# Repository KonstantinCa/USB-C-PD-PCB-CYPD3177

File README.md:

# USB-C Power Delivery PCB

**Note:** This project was developed as part of a university project. Technical references and documentation from the relevant companies/manufacturers, especially Infineon/Cypress documentation for the CYPD3177 USB-PD controller, were used as supporting sources for the design and analysis. The project is for educational and documentation purposes only.

This project focuses on the design and analysis of a USB-C Power Delivery sink system.  
The goal was to develop a custom PCB capable of requesting defined USB-PD voltage profiles from a USB-C Power Delivery charger.

The system is based on the Infineon/Cypress CYPD3177 USB-PD controller.  
An external microcontroller communicates with the controller via I2C in order to select different Power Delivery profiles and read status information such as the negotiated VBUS voltage.

## Project Overview

The project combines hardware design, embedded firmware and protocol analysis.  
The custom PCB was designed in KiCad and includes the required USB-C connector, USB-PD controller, power path circuitry, voltage regulation and communication interfaces.

## Features

- USB-C Power Delivery sink implementation
- CYPD3177 USB-PD controller integration
- Selection of different USB-PD voltage profiles
- I2C communication between microcontroller and USB-PD controller
- VBUS voltage measurement
- Interrupt-based response handling
- Finite State Machine firmware structure
- KiCad schematic and PCB layout
- Analysis of USB-PD, USB 2.0, I2C and UART communication

## Supported USB-PD Profiles

The firmware supports the following fixed supply PDO profiles:

| Profile | Voltage | Current |
|---|---:|---:|
| 1 | 5 V | 2 A |
| 2 | 9 V | 2 A |
| 3 | 12 V | 2.25 A |
| 4 | 15 V | 1.8 A |
| 5 | 20 V | 1.5 A |

## Firmware

The ESP32 firmware communicates with the CYPD3177 over I2C and allows the user to select a desired USB-PD profile via the serial monitor.

### Serial Commands

| Command | Function |
|---|---|
| `STATUS` | Reads the current status and response information |
| `5V2A` | Requests 5 V / 2 A |
| `9V2A` | Requests 9 V / 2 A |
| `12V2.25A` | Requests 12 V / 2.25 A |
| `15V1.8A` | Requests 15 V / 1.8 A |
| `20V1.5A` | Requests 20 V / 1.5 A |

### Firmware State Machine

The firmware is structured as a finite state machine:

```text
INIT -> IDLE -> SEND -> WAIT -> RECEIVE -> IDLE

The state machine waits for user input, checks whether a USB-PD contract is established, sends the selected PDO to the CYPD3177, waits for an interrupt, and then reads the response and VBUS voltage.

## Hardware Design

The PCB design contains the following main functional blocks:

- USB-C connector
- CYPD3177 USB Power Delivery controller
- Power path switching stage
- Buck converter for 3.3 V supply generation
- USB-to-UART interface for communication and debugging
- Microcontroller interface
- I2C communication lines
- UART communication lines
- Protection and configuration circuitry

The PCB was designed as a four-layer board with separate layers for signal routing, ground reference, and power distribution.

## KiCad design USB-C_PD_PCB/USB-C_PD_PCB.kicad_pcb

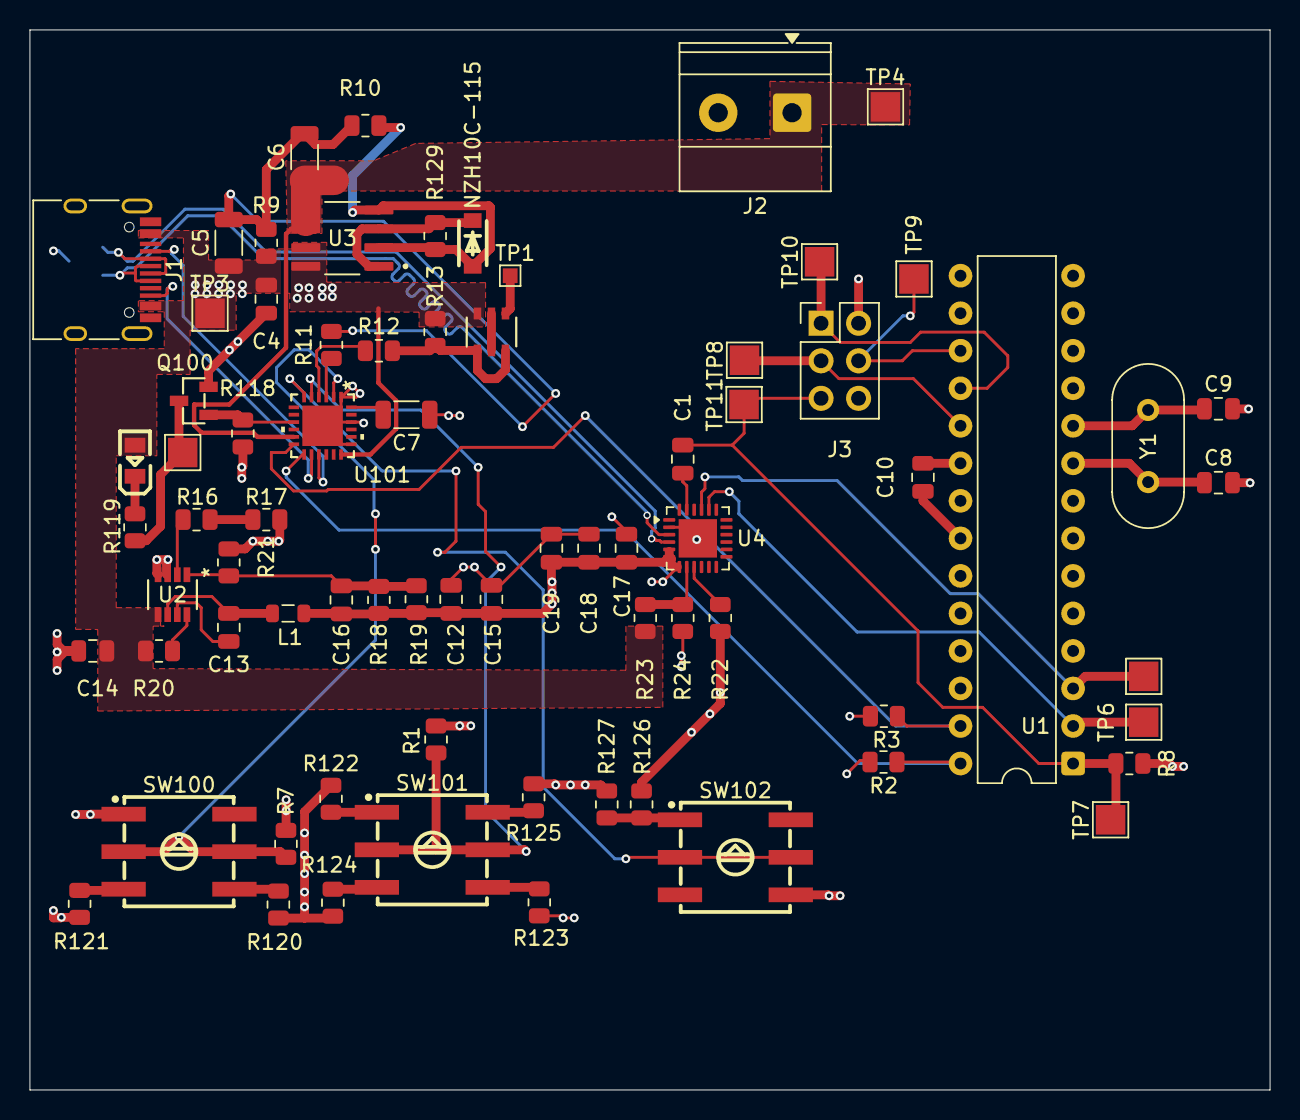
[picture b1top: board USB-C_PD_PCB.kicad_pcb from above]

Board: 4 copper layers, 83.9 x 71.8 mm, 75 parts (1 on the bottom side), 49 nets.

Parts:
BSL308PEH6327XTSA1: BSL308PEH6327XTSA1; PG-TSOP6-6-4_INF
C1: 4.7uF; C_0805_2012Metric
C4: 3.3uF; C_0805_2012Metric
C5, C6: 1uF; L_1206_3216Metric
C7: 100nF; L_1206_3216Metric
C8, C9: 22pF; C_0805_2012Metric
C10: ´10uF; C_0805_2012Metric
C12, C14, C15: 4u7; C_0805_2012Metric
C13: 100n; C_0805_2012Metric
C16: 10p; C_0805_2012Metric
C17, C18, C19: 100nF; C_0805_2012Metric
D1: ESDA5V3L; SOT-23-3
D101: LED PD; LED0805-R-RD
J1: USB4105-GF-A-060; USB_C_Receptacle_HRO_TYPE-C-31-M-12
J2: Screw_Terminal_01x02; TerminalBlock_Phoenix_MKDS-1,5-2_1x02_P5.00mm_Horizontal
J3: AVR-ISP-6; PinHeader_2x03_P2.54mm_Vertical
L1: 47u; L_0805_2012Metric
NZH10C-115: Zener Diode; SOD-123F_L2.8-W1.8-LS3.7-RD
Q100: NTR4503N; NTR4503NT1G-VB
R1, R7: 5k1; R_0805_2012Metric
R2, R3, R119: 1K; R_0805_2012Metric
R8, R11, R12, R22, R120: 1k; R_0805_2012Metric
R9: 10k; R_0805_2012Metric
R10: 0R; R_0805_2012Metric
R13: 49.9k; R_0805_2012Metric
R16, R17: 100k; R_0805_2012Metric
R18, R19: 2M; R_0805_2012Metric
R20: 20k; R_0805_2012Metric
R21: 222K; R_0805_2012Metric
R23: 180k; R_0805_2012Metric
R24: 33K; R_0805_2012Metric
R118: 100K 5%; R_0805_2012Metric
R121: 2.4k; R_0805_2012Metric
R122: 1 k; R_0805_2012Metric
R123, R127: 2.4 k; R_0805_2012Metric
R124, R126: 5.1 k; R_0805_2012Metric
R125: 10 k; R_0805_2012Metric
R129: 49.9K; R_0805_2012Metric
SW100: VBUS_Max; SW-SMD_MSSR-10S
SW101: Sink_Coarse; SW-SMD_MSSR-10S
SW102: Sink_fine; SW-SMD_MSSR-10S
TP1: TestPoint 5V; TestPoint_Pad_1.0x1.0mm
TP2, TP3, TP4, TP5, TP6, TP7, TP8, TP9, TP10, TP11: TestPoint; TestPoint_Pad_2.0x2.0mm
U1: ATmega328-P; DIP-28_W7.62mm
U2: SY8303AIC; TSOT_303AIC_SGY
U3: IRF9362TRPBF; SOIC127P600X175-8N
U4: CP2102N-Axx-xQFN24; QFN-24-1EP_4x4mm_P0.5mm_EP2.6x2.6mm
U101: CYPD3177-24LQXQT; QFN24_CYPD3177_INF
Y1: 8MHz; Crystal_HC49-U_Vertical

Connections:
+3.3V: C12.1, C15.1, C16.1, C17.1, C18.1, C19.1, J3.2 (VCC), L1.2, R1.1, R2.2, R3.2, R7.1, R8.2, R18.1, R19.1, R22.1, R126.1, U1.7 (VCC), U4.5 (VIO), U4.6 (VDD), U4.7 (VREGIN)
/GATE: NZH10C-115.2 (A), R10.1, R129.2, U3.2 (G1), U3.4 (G2)
/R_I_1A: R122.1, SW101.1
/R_I_2A: R123.1, SW101.2
/R_I_3A: R124.1, SW101.4
/R_I_4A: R125.1, SW101.8
/R_I_+500mA: R126.2, R127.1, SW102.1
/R_V_9V: R120.1, SW100.2
/R_V_12V: R121.1, SW100.4
/SOURCE: NZH10C-115.1 (K), R129.1, U3.1 (S1), U3.3 (S2)
CC1: J1.A5 (CC1), U101.15 (CC1)
CC2: J1.B5 (CC2), U101.14 (CC2)
D+: D1.2 (K), J1.A6 (DP1), J1.B6 (DP2), U4.3 (D+)
D-: D1.1 (K), J1.A7 (DN1), J1.B7 (DN2), U4.4 (D-)
GND: C4.1, C7.1, C8.2, C9.2, C10.2, C12.2, C14.2, C15.2, C17.2, C18.2, C19.2, D1.3 (A), J1.A1, J1.A12, J1.B1, J1.B12, J1.S1, J2.2, J3.6 (GND), Q100.2 (S), R17.1, R21.1, R24.2, R118.2, R120.2, R121.2, R122.2, R123.2, R124.2, R125.2, R127.2, SW100.1, SW102.2, U1.8 (GND), U1.22 (GND), U2.3 (GND), U2.4 (GND), U4.2 (GND), U4.25 (GND), U101.1 (VBUS_MIN), U101.19 (GND), U101.22 (VSS), U101.25 (EPAD)
ISNK_COARSE: R1.2, SW101.C, U101.5 (ISNK_COARSE)
ISNK_FINE: SW102.C, U101.6 (ISNK_FINE)
MISO: J3.1 (MISO), TP10.1, U1.18 (PB4)
MOSI: J3.4 (MOSI), TP9.1, U1.17 (PB3)
unnamed: BSL308PEH6327XTSA1.1, BSL308PEH6327XTSA1.3, R12.2, R13.1
unnamed: BSL308PEH6327XTSA1.2, BSL308PEH6327XTSA1.5
unnamed: BSL308PEH6327XTSA1.4, TP1.1
unnamed: C5.2, C6.2, R9.2, R10.2, R11.1
unnamed: D101.2 (K), R119.1
unnamed: Q100.3 (D), R119.2, TP2.1
unnamed: Q100.1 (G), R118.1, U101.9 (FAULT)
unnamed: R16.1, R17.2
unnamed: C10.1, U1.20 (AVCC)
unnamed: C8.1, U1.9 (XTAL1/PB6), Y1.1
unnamed: C9.1, U1.10 (XTAL2/PB7), Y1.2
unnamed: C13.1, U2.7 (BS)
unnamed: R20.2, U2.8 (EN)
unnamed: C16.2, R18.2, R19.2, R21.2, U2.1 (FB)
unnamed: R16.2, U2.2 (FS)
unnamed: C13.2, L1.1, U2.6 (LX)
unnamed: R23.2, R24.1, U4.8 (VBUS)
unnamed: R22.2, U4.9 (~RST)
unnamed: R11.2, U101.3 (VBUS_FET_EN)
unnamed: C7.2, U101.24 (VCCD)
RESET_uC: C1.2, J3.5 (~RST), R8.1, TP7.1, TP11.1, U1.1 (~RESET/PC6)
RXD_uC: TP5.1, U1.3 (PD1), U4.20 (RXD)
SAVE_PWR_EN: R12.1, U101.4 (SAFE_PWR_EN)
SCK: J3.3 (SCK), TP8.1, U1.19 (PB5)
SCL: R2.1, U1.28 (PC5), U101.13 (HPI_SCL)
SDA: R3.1, U1.27 (PC4), U101.12 (HPI_SDA)
TXD_uC: TP6.1, U1.2 (PD0), U4.21 (TXD)
VBUS_IN: BSL308PEH6327XTSA1.6, C4.2, C5.1, C14.1, D101.1 (A), J1.A4, J1.A9, J1.B4, J1.B9, R9.1, R13.2, R20.1, R23.1, TP3.1, U2.5 (IN), U3.7 (D1_2), U3.8 (D1), U101.18 (VBUS_IN)
VBUS_MAX: R7.2, SW100.C, U101.2 (VBUS_MAX)
VBUS_OUT: C6.1, J2.1, TP4.1, U3.5 (D2_2), U3.6 (D2), U101.11 (VDC_OUT)

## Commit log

2026-05-25 Add ESP32 firmware
2026-05-25 Add KiCad PCB design files
2026-05-25 Fix repository language detection
